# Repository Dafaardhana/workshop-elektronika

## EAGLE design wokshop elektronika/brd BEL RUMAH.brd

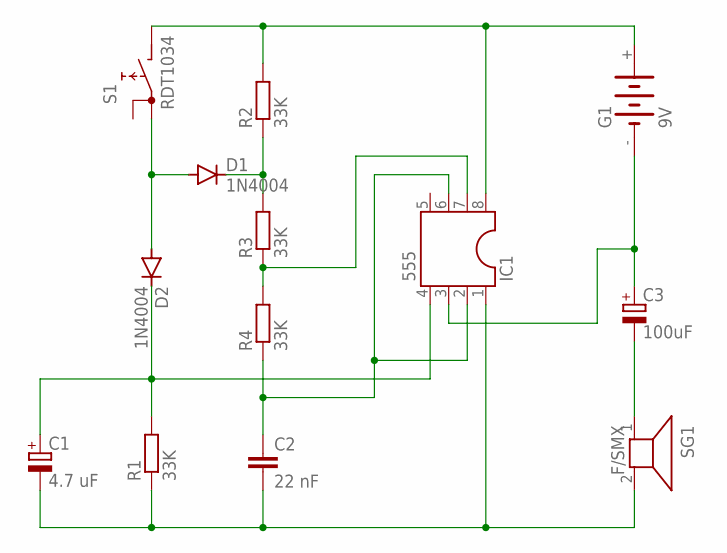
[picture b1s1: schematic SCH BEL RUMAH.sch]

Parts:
C1: 4.7 uF; TT2D5
C2: 22 nF; C025-024X044
C3: 100uF; TT2D5
D1, D2: 1N4004; DO41-10
G1: 9V; 3V11R
IC1: 555; DIL08
R1, R2, R3, R4: 33K; 0204/7
S1: RDT1034
SG1: F/SMX

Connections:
unnamed: G1.+, IC1.8, R2.2, S1.B
unnamed: D1.A, D2.A, S1.A1
unnamed: D1.C, R2.1, R3.2
unnamed: IC1.7, R3.1, R4.2
unnamed: C1.+, D2.C, IC1.4, R1.2
unnamed: C1.-, C2.2, IC1.1, R1.1, SG1.2
unnamed: C2.1, IC1.2, IC1.6, R4.1
unnamed: C3.-, SG1.1
unnamed: C3.+, G1.-, IC1.3

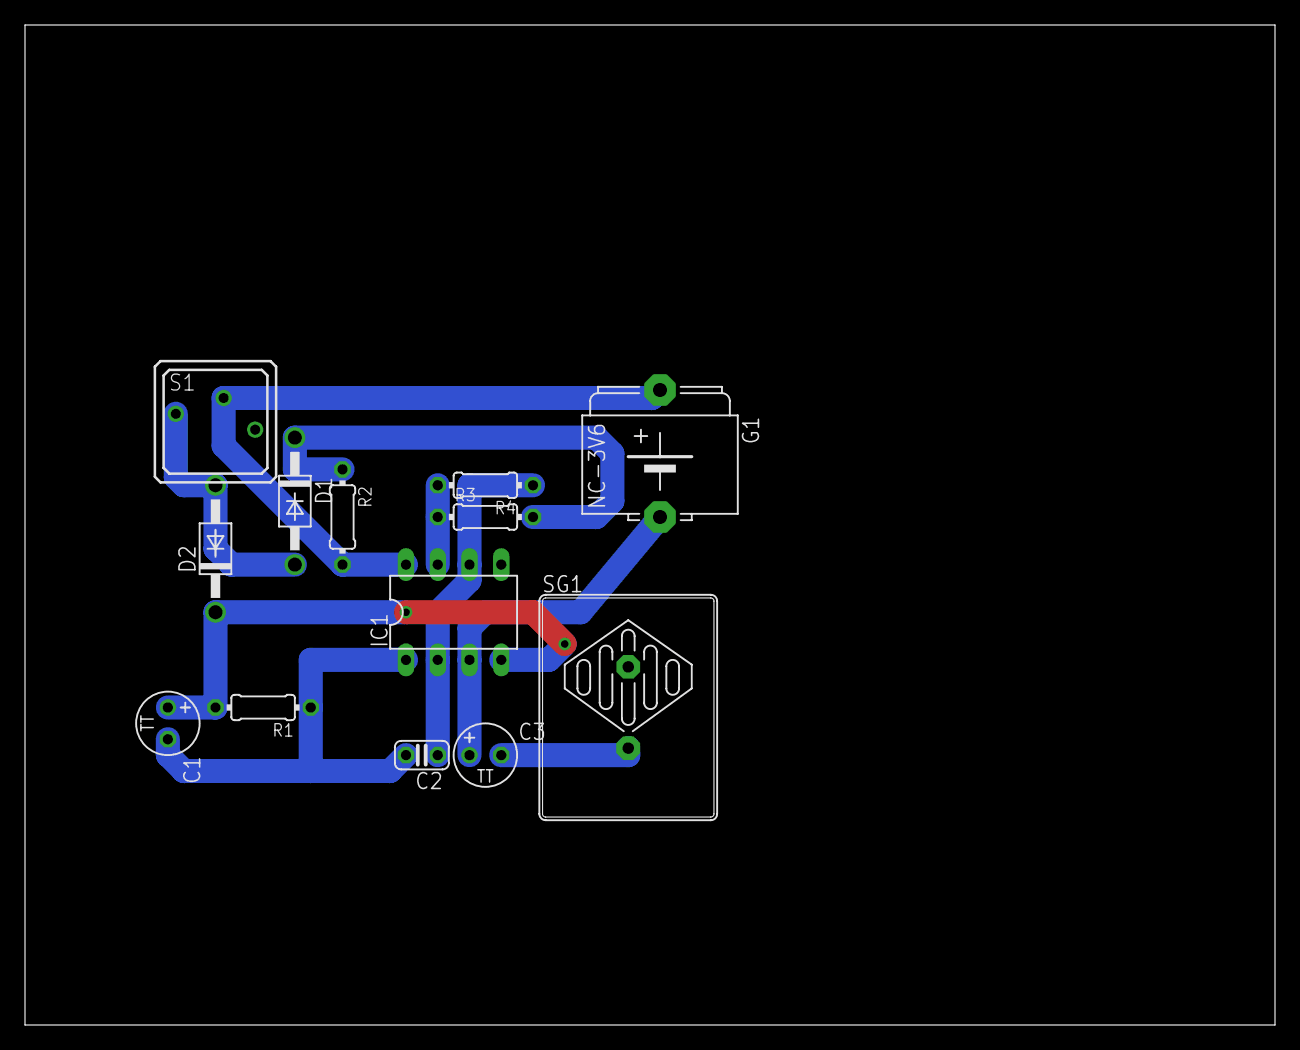
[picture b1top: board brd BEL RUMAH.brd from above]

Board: 2 copper layers, 100.0 x 80.0 mm, 13 parts (0 on the bottom side), 9 nets.
